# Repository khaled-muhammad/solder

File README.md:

# Two Bulb Blinker PCB — First Ever Soldered Project

## Project Description
This is my **first PCB project ever!** I built a simple **two-bulb blinker** with a small delay, using **only transistors and capacitors — no microcontrollers!**  

The LEDs blink **alternately with a delay**, controlled purely by electronic components.  

---

## 🔧 Bill of Materials (BOM)

| Component          | Quantity | Value / Type  |
|--------------------|----------|----------------|
| LED                | 2        | 5mm Any Color  |
| NPN Transistor     | 2        | 2N3904         |
| Resistor (LED)     | 2        | 220Ω           |
| Resistor (Base)    | 2        | 47kΩ           |
| Capacitor          | 2        | 10uF           |
| Power Supply       | 1        | CR2032 Battery |

---

## Schematic

---

## 3D View

---

## PCB Layout

---

## My Info
- **Slack Member ID:** `U08QKDF6F9B`  
- **Slack Full Name:** Khaled Muhammad Ibrahim  
- **Slack Display Name:** Khaled  

---

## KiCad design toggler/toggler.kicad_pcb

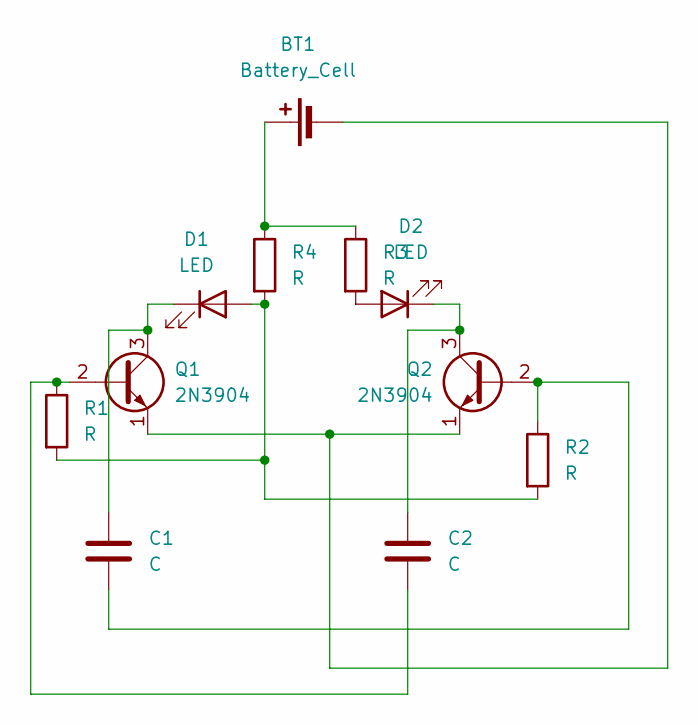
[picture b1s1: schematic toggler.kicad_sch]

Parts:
BT1: Battery_Cell; BatteryHolder_Keystone_3034_1x20mm
C1, C2: C; CP_Radial_D8.0mm_P5.00mm
D1, D2: LED; LED_D5.0mm
Q1, Q2: 2N3904; TO-92_Inline
R1, R2, R3, R4: R; R_Axial_DIN0207_L6.3mm_D2.5mm_P7.62mm_Horizontal

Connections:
unnamed: BT1.1 (+), R3.1, R4.1
unnamed: BT1.2 (-), Q1.1 (E), Q2.1 (E)
unnamed: D1.2 (A), R1.2, R2.2, R4.2
unnamed: C1.1, D1.1 (K), Q1.3 (C)
unnamed: D2.2 (A), R3.2
unnamed: C2.1, D2.1 (K), Q2.3 (C)
unnamed: C2.2, Q1.2 (B), R1.1
unnamed: C1.2, Q2.2 (B), R2.1

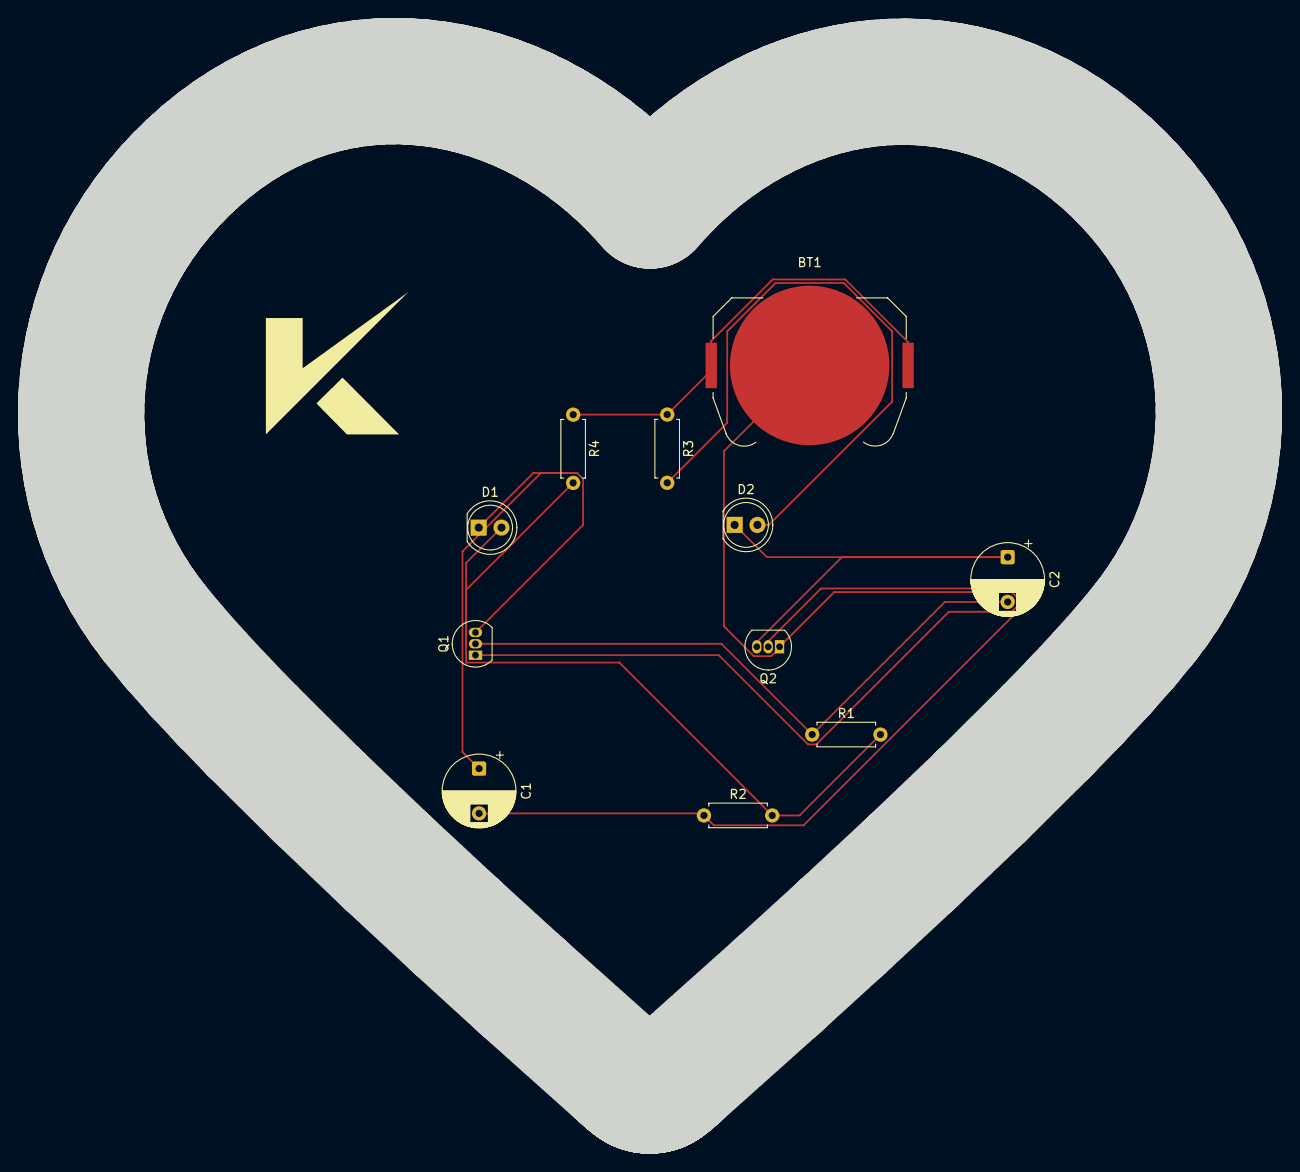
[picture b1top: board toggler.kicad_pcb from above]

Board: 2 copper layers, 127.0 x 112.7 mm, 11 parts (0 on the bottom side), 8 nets.

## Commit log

2025-06-25 Project files
